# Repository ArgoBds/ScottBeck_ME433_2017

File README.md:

# ScottBeck_ME433_2017
Class Repo
3/29/3017
Homework and Project Files will be committed here.

This is a test to see if a change is committed

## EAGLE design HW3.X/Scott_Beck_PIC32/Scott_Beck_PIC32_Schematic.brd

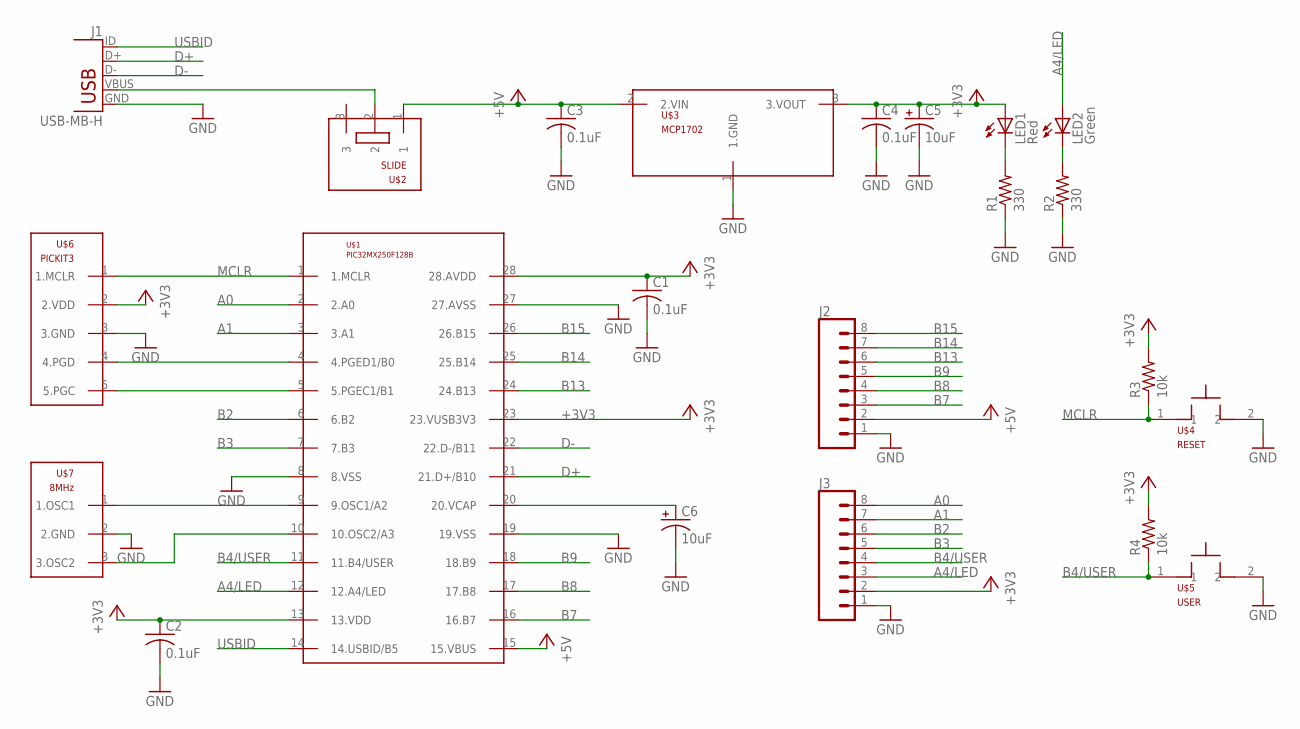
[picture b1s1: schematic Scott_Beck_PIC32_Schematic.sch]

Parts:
C1, C2, C3, C4: 0.1uF; C0603
C5, C6: 10uF; C0603
J1: USB-MB-H
J2, J3: CONN_08"; 1X08
LED1: Red; SML0603
LED2: Green; SML0603
R1, R2: 330; R0603
R3, R4: 10k; R0603
U$1: PIC32MX250F128B; DIL28-3
U$2: SLIDE
U$3: MCP1702; TO92
U$4: RESET; PB
U$5: USER; PB
U$6: PICKIT3
U$7: 8MHz; OSC

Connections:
+3V3: C1.1, C2.1, C4.1, C5.1, J3.2, LED1.A, R3.2, R4.2, U$1.13 (13.VDD), U$1.23 (23.VUSB3V3), U$1.28 (28.AVDD), U$3.3 (3.VOUT), U$6.2 (2.VDD)
+5V: C3.1, J2.2, U$1.15 (15.VBUS), U$2.1, U$3.2 (2.VIN)
A0: J3.8, U$1.2 (2.A0)
A1: J3.7, U$1.3 (3.A1)
A4/LED: J3.3, LED2.A, U$1.12 (12.A4/LED)
B2: J3.6, U$1.6 (6.B2)
B3: J3.5, U$1.7 (7.B3)
B4/USER: J3.4, R4.1, U$1.11 (11.B4/USER), U$5.1
B7: J2.3, U$1.16 (16.B7)
B8: J2.4, U$1.17 (17.B8)
B9: J2.5, U$1.18 (18.B9)
B13: J2.6, U$1.24 (24.B13)
B14: J2.7, U$1.25 (25.B14)
B15: J2.8, U$1.26 (26.B15)
D+: J1.D+, U$1.21 (21.D+/B10)
D-: J1.D-, U$1.22 (22.D-/B11)
GND: C1.2, C2.2, C3.2, C4.2, C5.2, C6.2, J1.GND, J2.1, J3.1, R1.1, R2.1, U$1.8 (8.VSS), U$1.19 (19.VSS), U$1.27 (27.AVSS), U$3.1 (1.GND), U$4.2, U$5.2, U$6.3 (3.GND), U$7.2 (2.GND)
MCLR: R3.1, U$1.1 (1.MCLR), U$4.1, U$6.1 (1.MCLR)
unnamed: J1.VBUS, U$2.2
unnamed: U$1.9 (9.OSC1/A2), U$7.1 (1.OSC1)
unnamed: LED1.C, R1.2
unnamed: U$1.10 (10.OSC2/A3), U$7.3 (3.OSC2)
unnamed: C6.1, U$1.20 (20.VCAP)
unnamed: LED2.C, R2.2
PGC: U$1.5 (5.PGEC1/B1), U$6.5 (5.PGC)
PGD: U$1.4 (4.PGED1/B0), U$6.4 (4.PGD)
USBID: J1.ID, U$1.14 (14.USBID/B5)

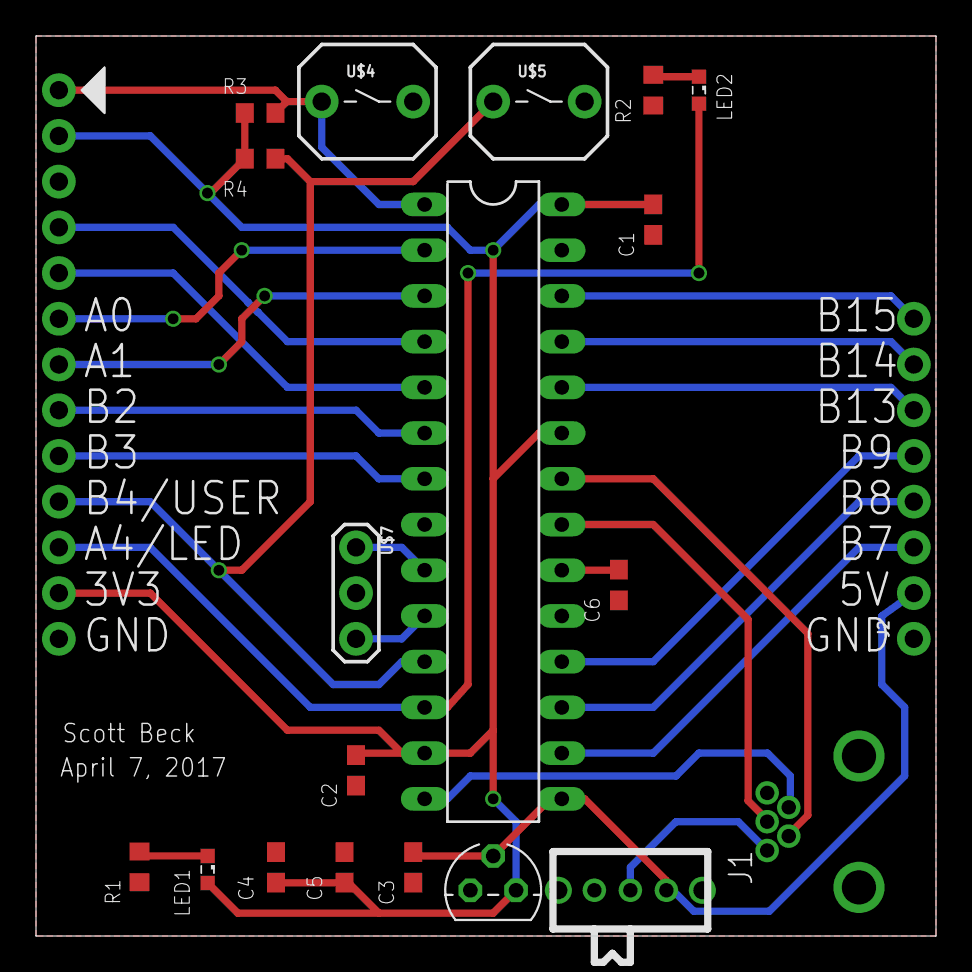
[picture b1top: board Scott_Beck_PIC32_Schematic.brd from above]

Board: 2 copper layers, 50.0 x 50.0 mm, 22 parts (0 on the bottom side), 27 nets.

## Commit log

2017-03-29 Committing for the first time.
2017-03-29 :tada: Added .gitattributes & .gitignore files
2017-03-29 Update
    First Change
2017-03-29 Creating Project
    First Project
2017-03-30 First Attempt
    Template PRAGMA populated and first attempt at code for PIC32
2017-03-31 Testing
    Simplifying Code to Test Functionality of PIC Circuit
2017-03-31 Final Code
    Fixed Code that functions as intended
2017-04-03 Creating Eagle Library
    Initial copying of existing schematics into new library and editting
    USB-MH design.
2017-04-03 Library Complete
    All Custom Library Files Completed
2017-04-04 Schematic
    Schematic for PIC32 Created and Finished
2017-04-06 Created HW3 Folder and Began Work on brd File
2017-04-06 Updated Board
    Began Design, Replaced res/cap with surface mounts.
2017-04-06 First Complete Board
    First Draft of Completed Board
2017-04-07 Semi-Finalized Board
    Pre-Final Checks
2017-04-07 GERBER Files
    Finalized Board and Made GERBER Files
2017-04-10 Completed Code for HW4
    Sorry that this is my only commit for this homework. I forgot to update
    throughout the debugging process.
2017-04-13 Functional HW5 Code
    Code seems to function on other students' hardware, but will not run on
    my board.
2017-04-17 HW6 Commit
    First Commit for HW6. First draft of LCD_drawChar
2017-04-18 Completed HW6
    Working drawString and barUpdate Functions
2017-04-20 Completed Code for HW7
    Working IMU code with LCD display
2017-04-27 First Harmony Commit
    HW8 Completed using Harmony Configurator.
2017-04-27 HW9 Commit
    Completed HW 9
2017-05-18 HW10 Complete and HW11 Generated
2017-05-19 HW12 Started
2017-05-19 HW12 Done
2017-05-19 HW13 Completed
2017-05-22 HW 14 PIC Code Completed
    Tested with putty
2017-05-22 HW14 Android Completed
    Working Communication b/w PIC32 and Phone
2017-06-02 HW 11 and 18
    HW 11 and 18 Completed
2017-06-02 HW 15
    Pictures of Designs
2017-06-02 HW 16 and 17
    Pictures of built box and wheel
2017-06-06 HW19
    Started HW19
2017-06-06 HW 19 First Working Iterate
2017-06-07 final project Android
    Crashes on Opening, even with PIC
2017-06-08 Final Project Pic32
2017-06-08 Separating Final Project and Final Project PIC
2017-06-08 MainActivity Modified
2017-06-09 Final Project Final Iteration
